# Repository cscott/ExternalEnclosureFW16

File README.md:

# Input Module Adapter

This is a USB-C adapter to mount and use two small Input Modules or
one medium Input Module (like a numeric keypad) outside
of a Framework Laptop 16.  Note that the actual pogo pin connector is a 
custom Framework part which they have not made generally available;
I am using a pair of alternate connectors from Molex which are compatible.

The PCB incorporates a 4-port USB 2.0 hub, so that both input module
slots can be active.  If you only need the leftmost input module connector
to be functional (because you only want to use a medium-size Input Module,
for example), then you can omit many of the components and populate R4/R7/R8
as indicated on the [schematic](./SpringAdapter.pdf).

Further discussion can be found on the Framework Community forums at
https://community.frame.work/t/external-usb-c-enclosure-for-input-modules/53695

## License
Input Modules © 2023 by Framework Computer Inc is licensed under CC BY 4.0.

This external enclosure is © 2024 by
C. Scott Ananian and is also licensed under CC BY 4.0.

To view a copy of this license,
visit http://creativecommons.org/licenses/by/4.0/

## Assembly and Fabrication

**THIS DESIGN HAS NOT YET BEEN TESTED. CAVEAT LECTOR.**

This has been designed for PCBA by JLCPCB, and appropriate LCSC parts
numbers are included in the kicad files.  Hand soldering the molex
input module connectors may be required, as JLC does not tend to keep
these in stock -- although you can special order them, you might
find it easier to [obtain them from DigiKey](https://www.digikey.com/en/products/detail/molex/0472861001/4553726)
and hand-solder them (or use a hot plate).

Use a 0.8mm PCB.  The needed files for JLCPCB fabrication are in
the [production](./production) directory.  Use `bom.csv` and `positions.csv`
for PCBA.

The enclosure and lid have been designed in FreeCad.  Some of the tolerances
and thicknesses might be challenging to print on a home 3d printer; I had
JLCPCB print these using SLS in black nylon; the STEP files are provided
in [External Enclosure.step](./External%20Enclosure.step) and
[Lid.step](./Lid.step).

To make Input Modules attach to the
adapter, you can glue in 5mm x 2mm cylindrical magnets or glue on
5mm x 5mm x 1.2mm square magnets.

There are recesses on the bottom surface for <=8mm rubber bumper feet,
like [these from DigiKey](https://www.digikey.com/en/products/detail/3m/SJ5076/570288) (but you can get these anywhere).

Use M2x6mm flathead fasteners as the alignment pins, with a M2 nut on the top
of the PCB (which also serves to secure the PCB in the case).  You can
probably get away with using pan head fasteners if the rubber bumpers are
tall enough.

There are cutouts for 3mm x 1.5mm cylindrical magnets on the front face
and on the lid to secure the lid.  Ensure the polarities are appropriate
such that the lid is attracted to the body of the enclosure!

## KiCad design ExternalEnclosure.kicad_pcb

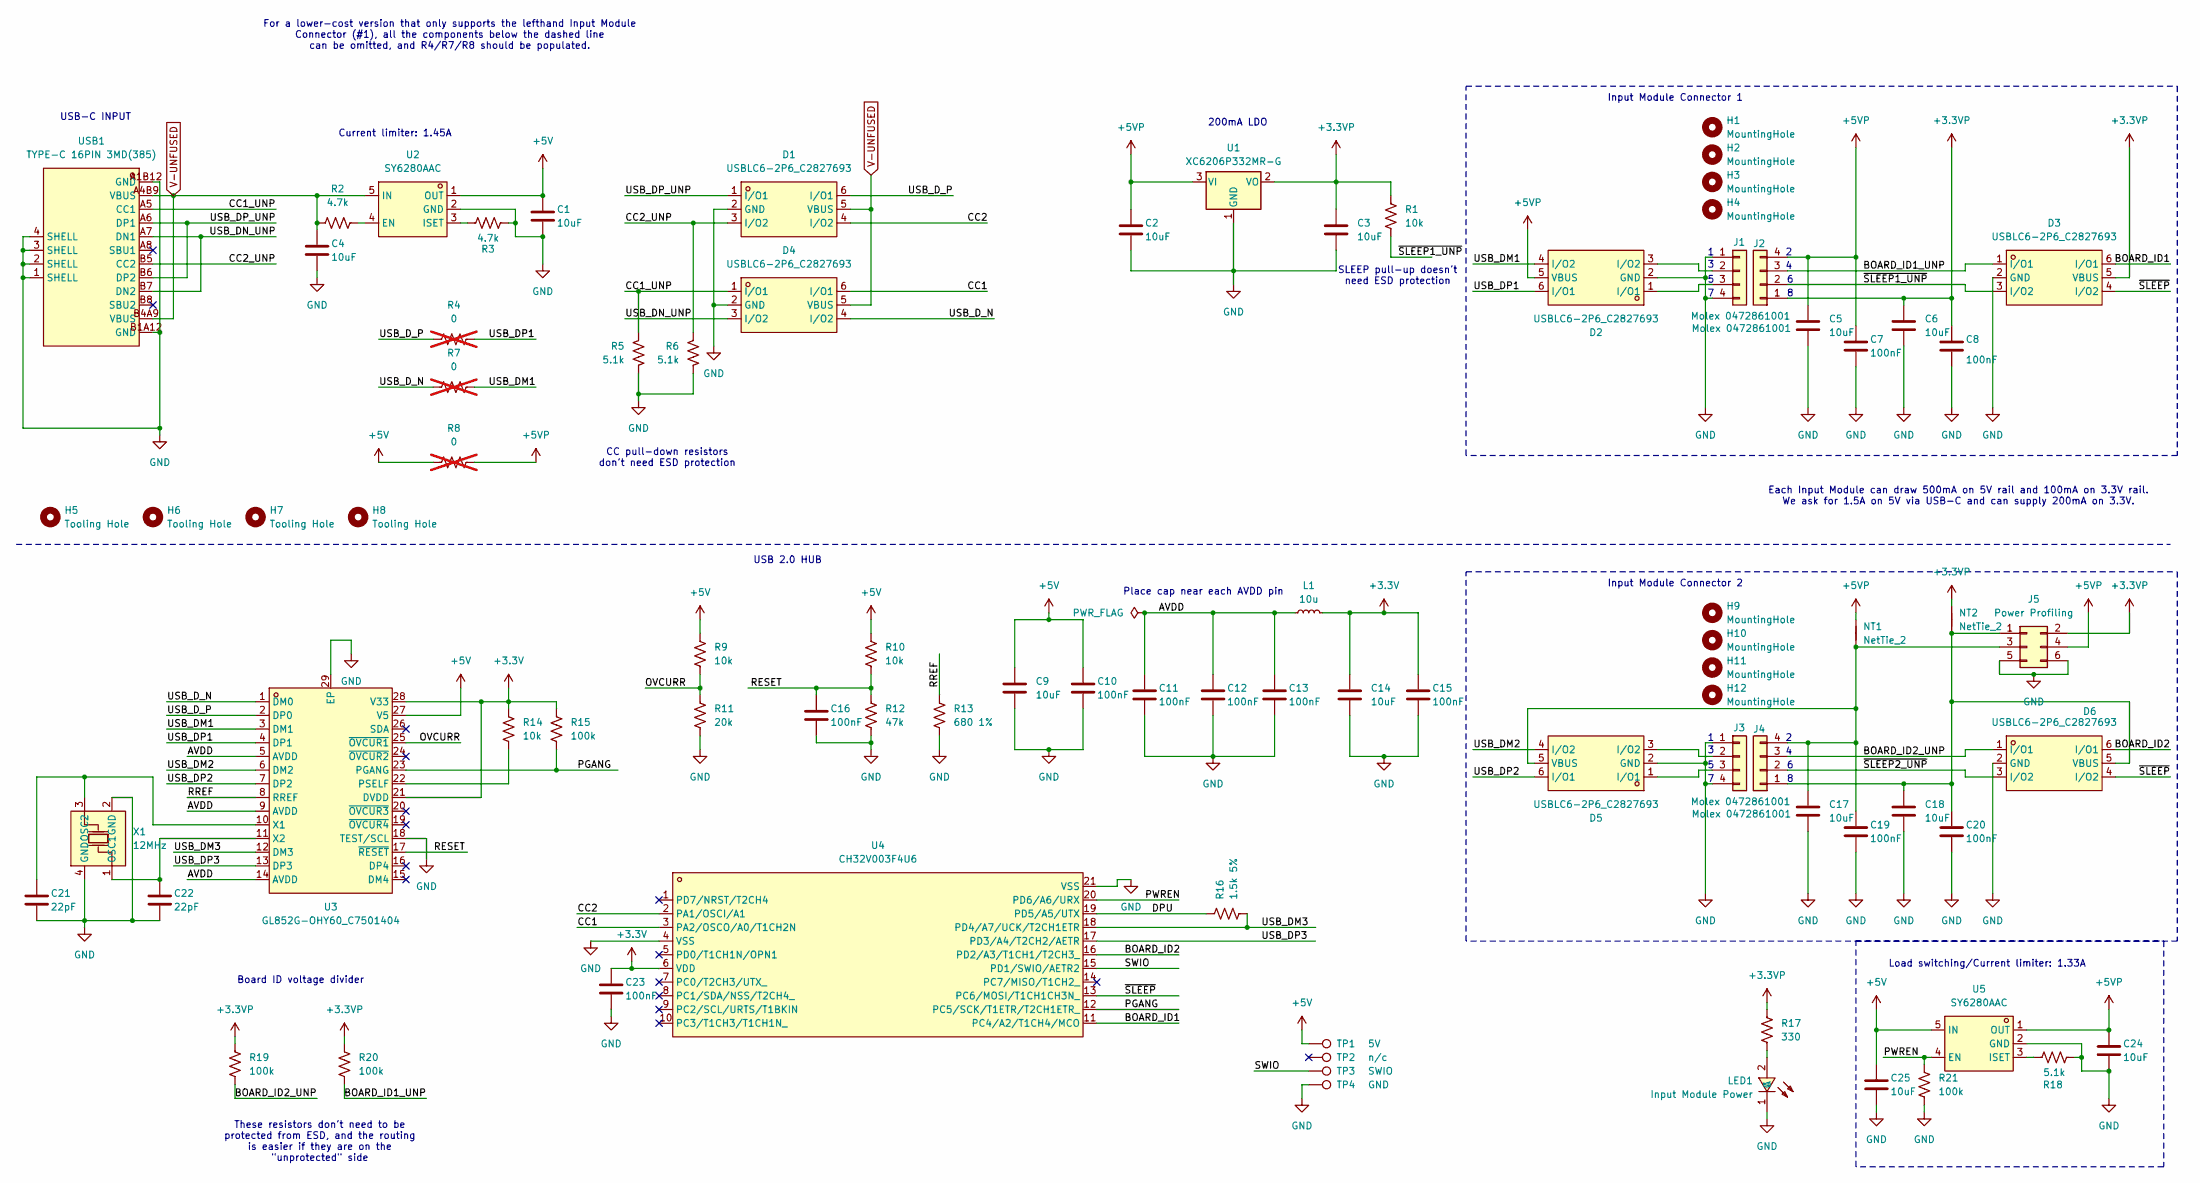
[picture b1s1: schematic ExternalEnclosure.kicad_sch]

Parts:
C1, C2, C3, C4, C5, C6, C9, C14, C17, C18, C24, C25: 10uF; C_0603_1608Metric; LCSC Part C96446
C7, C8, C10, C11, C12, C13, C15, C16, C19, C20, C23: 100nF; C_0402_1005Metric; LCSC Part C1525
C21, C22: 22pF; C_0402_1005Metric; LCSC Part C1555
D1, D2, D3, D4, D5, D6: USBLC6-2P6_C2827693; SOT-666-6_L1.6-W1.2-P0.50-LS1.6-BL; LCSC Part C2827693
H1, H2, H9, H10: MountingHole; MountingHole_5mm_slot_no_keepout
H3, H4, H11, H12: MountingHole; MountingHole_2.5mm
H5, H6, H7, H8: Tooling Hole; JLCPCB Tooling Hole
J1, J2, J3, J4: Molex 0472861001; Molex_0472861001; LCSC Part C6961828
J5: Power Profiling; PinHeader_2x03_P2.54mm_Vertical_SMD
L1: 10u; L_0805_2012Metric; LCSC Part C1046
LED1: Input Module Power; LED0603-RD-YELLOW; LCSC Part C72038
NT1, NT2: NetTie_2; NetTie-2_SMD_Pad0.5mm
R1, R9, R10, R14: 10k; R_0402_1005Metric; LCSC Part C25744
R2, R3: 4.7k; R_0402_1005Metric; LCSC Part C25900
R4, R7, R8: 0; R_0402_1005Metric; LCSC Part C17168; not fitted
R5, R6, R18: 5.1k; R_0402_1005Metric; LCSC Part C25905
R11: 20k; R_0402_1005Metric; LCSC Part C25765
R12: 47k; R_0402_1005Metric; LCSC Part C25792
R13: 680 1%; R_0603_1608Metric; LCSC Part C23228
R15, R19, R20, R21: 100k; R_0402_1005Metric; LCSC Part C25741
R16: 1.5k 5%; R_0402_1005Metric; LCSC Part C25867
R17: 330; R_0402_1005Metric; LCSC Part C25104
TP1: 5V; TestPoint_Pad_1.5x1.5mm
TP2: n/c; TestPoint_Pad_1.5x1.5mm
TP3: SWIO; TestPoint_Pad_1.5x1.5mm
TP4: GND; TestPoint_Pad_1.5x1.5mm
U1: XC6206P332MR-G; SOT-23-3; LCSC Part C5446
U2, U5: SY6280AAC; SOT-23-5_L3.0-W1.7-P0.95-LS2.8-BL; LCSC Part C55136
U3: GL852G-OHY60_C7501404; QFN-28_L5.0-W5.0-P0.50-BL-EP; LCSC Part C7501404
U4: CH32V003F4U6; QFN-20_L3.0-W3.0-P0.40-TL-EP1.7; LCSC Part C5299908
USB1: TYPE-C 16PIN 3MD(385); USB-C-SMD_TYPE-C16PIN; LCSC Part C2858270
X1: 12MHz; OSC-SMD_4P-L3.2-W2.5-BL; LCSC Part C9002

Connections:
+3.3V: C14.1, C15.1, C23.1, L1.2, R14.1, R15.1, U3.21 (DVDD), U3.28 (V33), U4.6 (VDD)
+3.3VP: C3.1, C6.1, C8.1, D3.5 (VBUS), J2.1, J5.2, NT2.2, R1.1, R17.1, R19.1, R20.1, U1.2 (VO)
+5V: C1.1, C9.1, C10.1, C25.1, R8.1, R9.1, R10.1, TP1.1, U2.1 (OUT), U3.27 (V5), U5.5 (IN)
+5VP: C2.1, C5.1, C7.1, C24.1, D2.5 (VBUS), J2.4, J5.4, NT1.2, R8.2, U1.3 (VI), U5.1 (OUT)
/AVDD: C11.1, C12.1, C13.1, L1.1, U3.5 (AVDD), U3.9 (AVDD), U3.14 (AVDD)
/BOARD_ID1: D3.6 (I/O1), U4.11 (PC4/A2/T1CH4/MCO)
/BOARD_ID1_UNP: D3.1 (I/O1), J2.3, R20.2
/BOARD_ID2: D6.6 (I/O1), U4.16 (PD2/A3/T1CH1/T2CH3_)
/BOARD_ID2_UNP: D6.1 (I/O1), J4.3, R19.2
/CC1: D4.6 (I/O1), U4.3 (PA2/OSCO/A0/T1CH2N)
/CC1_UNP: D4.1 (I/O1), R5.1, USB1.A5 (CC1)
/CC2: D1.4 (I/O2), U4.2 (PA1/OSCI/A1)
/CC2_UNP: D1.3 (I/O2), R6.1, USB1.B5 (CC2)
/DPU: R16.1, U4.19 (PD5/A5/UTX)
/OVCURR: R9.2, R11.1, U3.25 (~OVCUR1)
/PGANG: R15.2, U3.23 (PGANG), U4.12 (PC5/SCK/T1ETR/T2CH1ETR_)
/PWREN: R21.1, U4.20 (PD6/A6/URX), U5.4 (EN)
/RESET: C16.1, R10.2, R12.1, U3.17 (~RESET)
/RREF: R13.1, U3.8 (RREF)
/SWIO: TP3.1, U4.15 (PD1/SWIO/AETR2)
/USB_DM1: D2.4 (I/O2), R7.2, U3.3 (DM1)
/USB_DM2: D5.4 (I/O2), U3.6 (DM2)
/USB_DM3: R16.2, U3.12 (DM3), U4.18 (PD4/A7/UCK/T2CH1ETR)
/USB_DN_UNP: D4.3 (I/O2), USB1.A7 (DN1), USB1.B7 (DN2)
/USB_DP1: D2.6 (I/O1), R4.2, U3.4 (DP1)
/USB_DP2: D5.6 (I/O1), U3.7 (DP2)
/USB_DP3: U3.13 (DP3), U4.17 (PD3/A4/T2CH2/AETR)
/USB_DP_UNP: D1.1 (I/O1), USB1.A6 (DP1), USB1.B6 (DP2)
/USB_D_N: D4.4 (I/O2), R7.1, U3.1 (DM0)
/USB_D_P: D1.6 (I/O1), R4.1, U3.2 (DP0)
/~SLEEP1_UNP: D3.3 (I/O2), J2.2, R1.2
/~SLEEP2_UNP: D6.3 (I/O2), J4.2
/~SLEEP: D3.4 (I/O2), D6.4 (I/O2), U4.13 (PC6/MOSI/T1CH1CH3N_)
GND: C1.2, C2.2, C3.2, C4.2, C5.2, C6.2, C7.2, C8.2, C9.2, C10.2, C11.2, C12.2, C13.2, C14.2, C15.2, C16.2, C17.2, C18.2, C19.2, C20.2, C21.2, C22.2, C23.2, C24.2, C25.2, D1.2 (GND), D2.2 (GND), D3.2 (GND), D4.2 (GND), D5.2 (GND), D6.2 (GND), J1.1, J1.4, J3.1, J3.4, J5.5, J5.6, LED1.1 (C), R3.2, R5.2, R6.2, R11.2, R12.2, R13.2, R18.1, R21.2, TP4.1, U1.1 (GND), U2.2 (GND), U3.18 (TEST/SCL), U3.29 (EP), U4.4 (VSS), U4.21 (VSS), U5.2 (GND), USB1.1 (SHELL), USB1.2 (SHELL), USB1.3 (SHELL), USB1.4 (SHELL), USB1.A1B12 (GND), USB1.B1A12 (GND), X1.2 (GND), X1.4 (GND)
unnamed: C17.1, C19.1, D5.5 (VBUS), J4.4, J5.3, NT1.1
unnamed: C18.1, C20.1, D6.5 (VBUS), J4.1, J5.1, NT2.1
unnamed: D2.3 (I/O2), J1.2
unnamed: D2.1 (I/O1), J1.3
unnamed: D5.3 (I/O2), J3.2
unnamed: D5.1 (I/O1), J3.3
unnamed: LED1.2 (A), R17.2
unnamed: R2.2, U2.4 (EN)
unnamed: R3.1, U2.3 (ISET)
unnamed: R14.2, U3.22 (PSELF)
unnamed: C21.1, U3.10 (X1), X1.3 (OSC2)
unnamed: C22.1, U3.11 (X2), X1.1 (OSC1)
unnamed: R18.2, U5.3 (ISET)
V-UNFUSED: C4.1, D1.5 (VBUS), D4.5 (VBUS), R2.1, U2.5 (IN), USB1.A4B9 (VBUS), USB1.B4A9 (VBUS)

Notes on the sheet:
Place cap near each AVDD pin
200mA LDO
CC pull-down resistors don't need ESD protection
Board ID voltage divider
USB-C INPUT
Load switching/Current limiter: 1.33A
Input Module Connector 2
Input Module Connector 1
USB 2.0 HUB
Current limiter: 1.45A
These resistors don't need to be protected from ESD, and the routing is easier if they are on the "unprotected" side
SLEEP pull-up doesn't need ESD protection
Each Input Module can draw 500mA on 5V rail and 100mA on 3.3V rail. We ask for 1.5A on 5V via USB-C and can supply 200mA on 3.3V.
For a lower-cost version that only supports the lefthand Input Module Connector (#1), all the components below the dashed line can be omitted, and R4/R7/R8 should be populated.

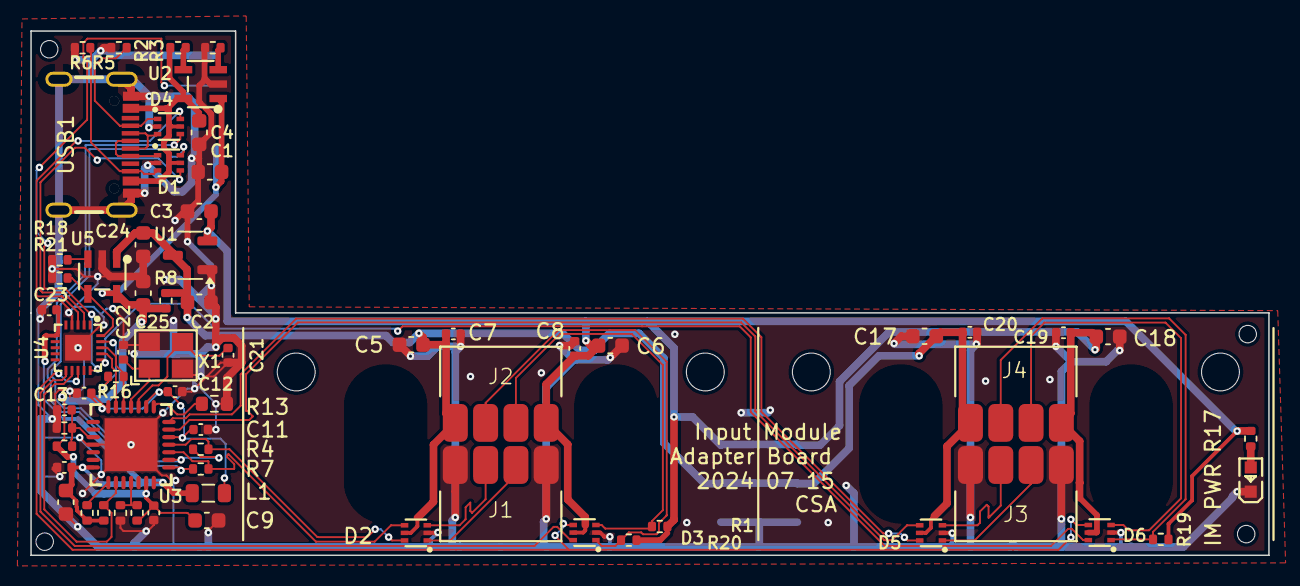
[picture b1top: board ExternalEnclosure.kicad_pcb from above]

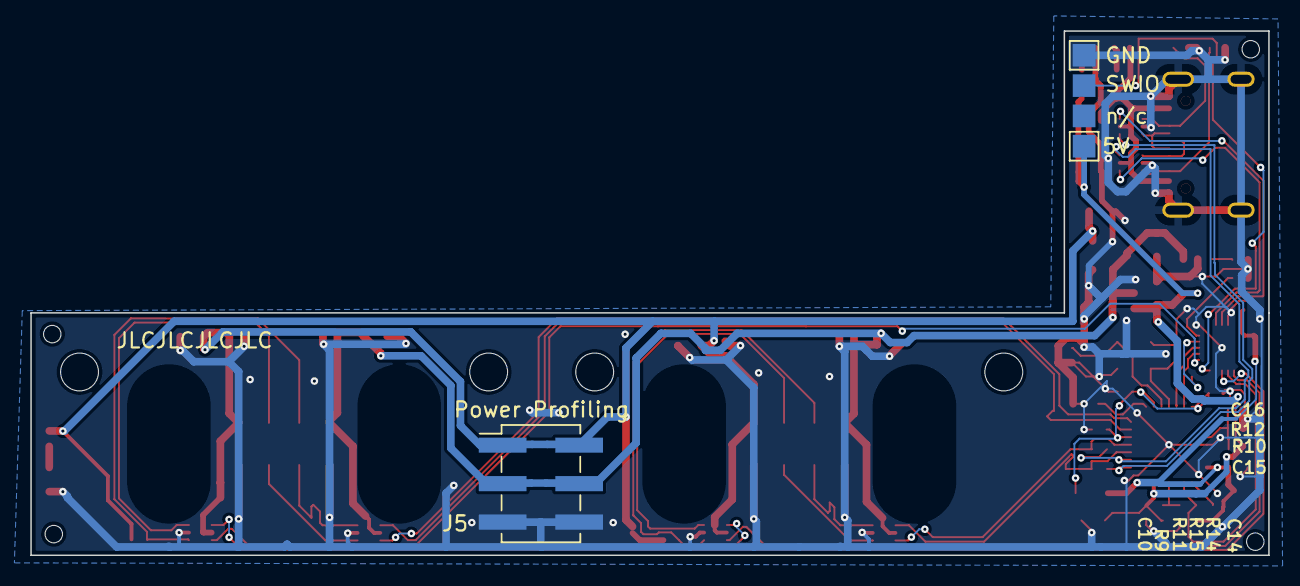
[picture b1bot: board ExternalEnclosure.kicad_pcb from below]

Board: 2 copper layers, 81.7 x 34.6 mm, 84 parts (7 on the bottom side), 48 nets.

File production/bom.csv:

Designator,Footprint,Quantity,Value,LCSC Part #
"C1, C14, C17, C18, C2, C24, C25, C3, C4, C5, C6, C9",0603,12,10uF,C96446
"C10, C11, C12, C13, C15, C16, C19, C20, C23, C7, C8",0402,11,100nF,C1525
"C21, C22",0402,2,22pF,C1555
"D1, D2, D3, D4, D5, D6",SOT-666-6_L1.6-W1.2-P0.50-LS1.6-BL,6,USBLC6-2P6_C2827693,C2827693
"J1, J2, J3, J4",Molex_0472861001,4,Molex 0472861001,C6961828
J5,PinHeader_2x03_P2.54mm_Vertical_SMD,1,Power Profiling,
L1,0805,1,10u,C1046
LED1,LED0603-RD-YELLOW,1,Input Module Power,C72038
"R1, R10, R14, R9",0402,4,10k,C25744
R11,0402,1,20k,C25765
R12,0402,1,47k,C25792
R13,0603,1,680 1%,C23228
"R15, R19, R20, R21",0402,4,100k,C25741
R16,0402,1,1.5k 5%,C25867
R17,0402,1,330,C25104
"R18, R5, R6",0402,3,5.1k,C25905
"R2, R3",0402,2,4.7k,C25900
U1,SOT-23-3,1,XC6206P332MR-G,C5446
"U2, U5",SOT-23-5_L3.0-W1.7-P0.95-LS2.8-BL,2,SY6280AAC,C55136
U3,QFN-28_L5.0-W5.0-P0.50-BL-EP,1,GL852G-OHY60_C7501404,C7501404
U4,QFN-20_L3.0-W3.0-P0.40-TL-EP1.7,1,CH32V003F4U6,C5299908
USB1,USB-C-SMD_TYPE-C16PIN,1,TYPE-C 16PIN 3MD(385),C2858270
X1,OSC-SMD_4P-L3.2-W2.5-BL,1,12MHz,C9002

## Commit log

2024-06-25 Initialize repository based on the "Spring Adapter" example from Framework
2024-06-29 Update repo to match JLCPCB parts, start adding USB hub
2024-06-30 First version complete
2024-06-30 Enclosure design, part 1
2024-07-01 Move USB-C adapter up 1mm
2024-07-01 DFM work
2024-07-01 First complete version of external enclosure
2024-07-01 more work on external enclosure
2024-07-01 Documentation updates!
2024-07-01 Fix the digikey link; add another picture
2024-07-02 Tweak 3d shapes for manufacturability
    Thinnest wall is now >= 0.8mm.
2024-07-02 Add link to forum thread
2024-07-07 Schematic/board v2: add CH32V003 to read board ID and control power/sleep
    The microcontroller allows us to actually monitor the BOARD_ID and USB CC1/2
    lines to monitor and control power consumption. It uses the unused 3rd
    USB port on the hub. ESD protection has also been added to all touchable
    connectors. A programming connector for the CH32V003 has been added based
    on the same molex 2mm-pitch spring connector we use for input modules.
    CH32V003 USB interface based on
2024-07-11 Fix part rotations for assembly
2024-07-11 Rename to ExternalMount (temporarily)
2024-07-11 Rename KiCad project to ExternalEnclosure
2024-07-12 Add back side SMT header for power profiling
2024-07-16 Tweak bottom clearances, change to slot for magnets on PCB
    The bottom clearances weren't quite right around the pogo pin area, and
    although my own PCBs made appropriate contact with the pogo pins, the
    official Framework LED Matrix input module was about 1mm (!) short of
    proper contact with the pins/magnet. A couple of things:
    * My "5mm diameter x 2mm thick" magnets were actually only 1.6mm thick
    * It appears that we need an extra 0.5mm clearance between the "thick
